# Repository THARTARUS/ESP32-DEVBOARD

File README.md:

# ESP32-DEVBOARD
this board is not tested (yet).
this devboard have:
1)  1 esp32-solo module
2)  1 I2C LUX SENSOR (VEML6030), with 0x10 ADDRESS
2)  2 12mm button with RC filter
3)  6 LED RED on 0603 format drived with only 3 I/O
4)  1 rotary ENCODER (to choose if you want the HOLLOWSHAFT named EC10E1260502 or a BOURNS encoder from the family PEC12R)
5)  1 BUZZER (SMD or 12mmTHT) or a SPEAKER (you can choose which one you need) drived with a NMOSFET sot23
6)  1 POWER OUTPUT (a sot23 PMOSFET drived by an NPN BJT)
7)  1 I2C temperature and humidity sensor (AHT20), with 0x37 ADDRESS
8)  1 2.42inch OLED display with I2C comunication, with 0x3C or 0x3D ADDRESS
9)  1 USB type-C connection (without PD) with a serial converter
10) 1 battery backup circuit with a charger (MCP7833 with charging up to 1A) and protection circuit DW01A)
11) 1 Power connection with USB/5V external supply priority and a DCDC with high efficency and VIn from 6V to 15V
12) 1 switching DCDC BUCKBOOST for the 3.3V power supply of the devboard and external circuit (with external load up to 600mA )
13) 1 expansion I/O with:
                          2 only analog INPUT
                          1 3x2 pin for external 3.3V supply need
                          1 JST-PH 1x04 for STEMMA and QWIIC sensor connected to the I2C line used for the other component on the board
                          1 SPI port (VPSI for DMA working) and the I2C connected with the JST-PH comunication line

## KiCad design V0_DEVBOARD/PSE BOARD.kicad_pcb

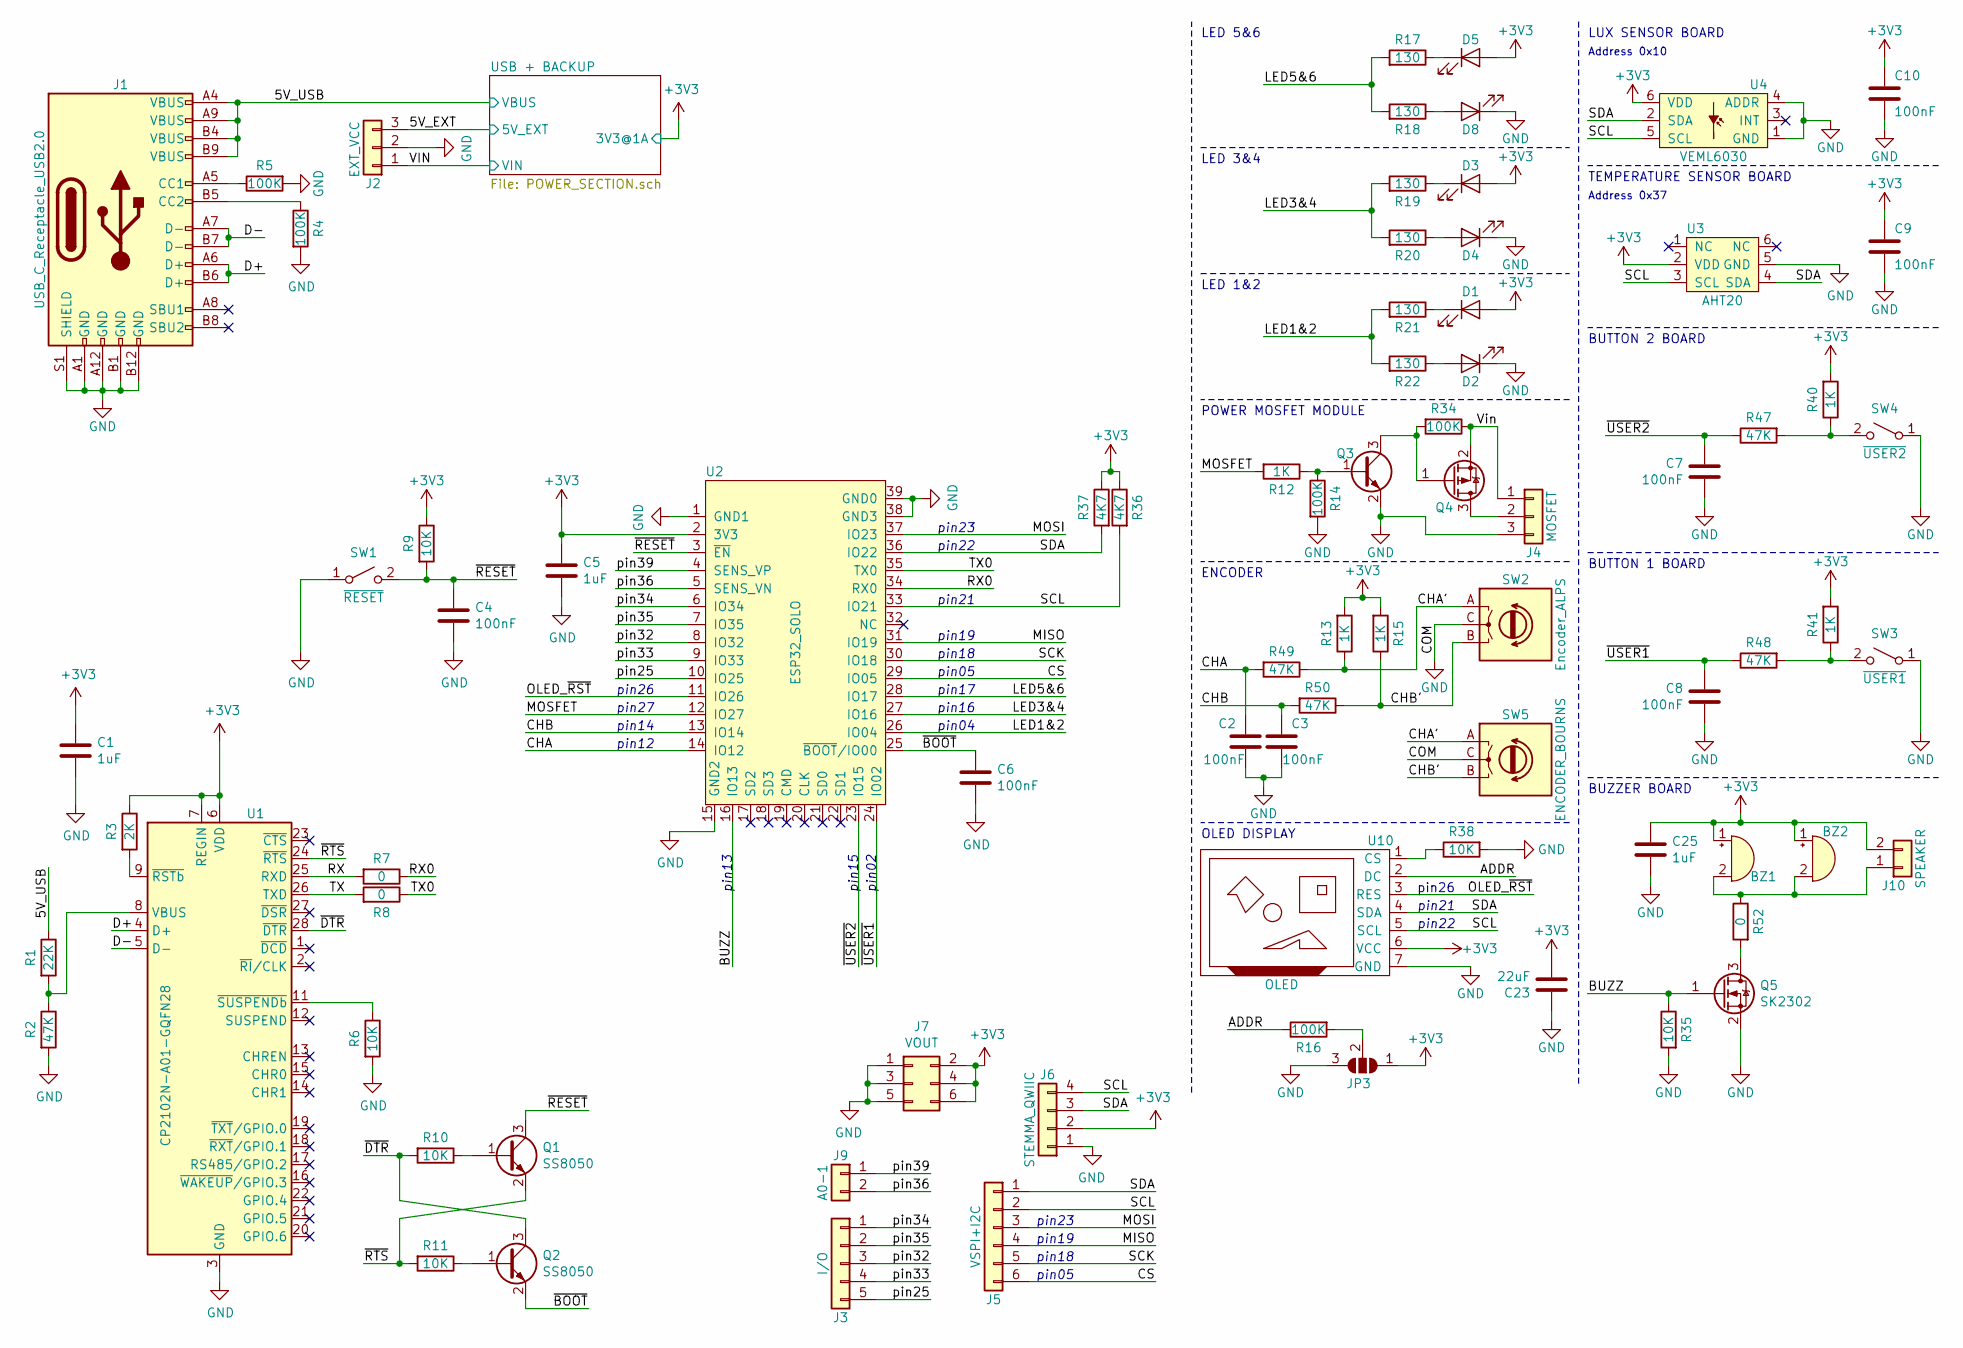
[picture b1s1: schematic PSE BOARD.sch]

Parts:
BZ1: Buzzer; Buzzer_CUI_CPT-9019S-SMT
BZ2: Buzzer; Buzzer_12x9.5RM7.6
C1, C5, C25: 1uF; C_0805_2012Metric
C2, C3, C4, C6, C7, C8, C9, C10: 100nF; C_0402_1005Metric
C23: 22uF; C_1210_3225Metric
D1, D2, D3, D4, D5, D8: LED; LED_0603_1608Metric_Castellated
J1: USB_C_Receptacle_USB2.0; USB_C_Receptacle_HRO_TYPE-C-31-M-12
J2: EXT_VCC; PinHeader_1x03_P2.54mm_Vertical
J3: I/O; PinHeader_1x05_P2.54mm_Vertical
J4: MOSFET; PinHeader_1x03_P2.54mm_Vertical
J5: VSPI+I2C; PinHeader_1x06_P2.54mm_Vertical
J6: STEMMA_QWIIC; JST_SH_SM04B-SRSS-TB_1x04-1MP_P1.00mm_Horizontal
J7: VOUT; PinHeader_2x03_P2.54mm_Vertical
J9: A0-1; PinHeader_1x02_P2.54mm_Vertical
J10: SPEAKER; JST_PH_B2B-PH-K_1x02_P2.00mm_Vertical
JP3: SolderJumper_3_Open; SolderJumper-3_P1.3mm_Open_RoundedPad1.0x1.5mm
Q1, Q2: SS8050; SOT-323_SC-70
Q3: LMBT3904WT1G; SOT-323_SC-70
Q4: SSM3J332R; SOT-23F
Q5: SK2302; SOT-23
R1: 22K; R_0402_1005Metric
R2, R47, R48, R49, R50: 47K; R_0402_1005Metric
R3: 2K; R_0402_1005Metric
R4, R5, R14, R16, R34: 100K; R_0402_1005Metric
R6, R9, R10, R11, R35, R38: 10K; R_0402_1005Metric
R7, R8: 0; R_0402_1005Metric
R12, R13, R15, R40, R41: 1K; R_0402_1005Metric
R17, R18, R19, R20, R21, R22: 130; R_0603_1608Metric
R36, R37: 4K7; R_0402_1005Metric
R52: 0; R_0805_2012Metric
SW1: ~RESET~; SW_SPST_4.5mmx4.5mm
SW2: Encoder_ALPS; RotaryEncoder_Alps_EC10E_HORIZONTAL
SW3: ~USER1~; 12x12mm_THT_OMRON_B3F
SW4: ~USER2~; 12x12mm_THT_OMRON_B3F
SW5: ENCODER_BOURNS; PEC12R
U1: CP2102N-A01-GQFN28; QFN-28-1EP_5x5mm_P0.5mm_EP3.35x3.35mm
U2: ESP32_SOLO; ESP32-WROOM-32
U3: AHT20; AHT20_package
U4: VEML6030; VEML6030_PACKAGE
U10: OLED

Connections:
+3V3: BZ1.1 (-), BZ2.1 (-), C1.1, C5.1, C9.1, C10.1, C23.2, C25.1, D1.2 (A), D3.2 (A), D5.2 (A), J6.2, J7.2, J7.4, J7.6, J10.2, JP3.1 (A), R3.1, R9.1, R13.2, R15.2, R36.1, R37.1, R40.2, R41.2, U1.6 (VDD), U1.7 (REGIN), U2.2 (3V3), U3.2 (VDD), U4.6 (VDD), U10.6 (VCC); also elsewhere on the board
/5V_EXT: J2.3; also elsewhere on the board
/5V_USB: J1.A4 (VBUS), J1.A9 (VBUS), J1.B4 (VBUS), J1.B9 (VBUS), R1.1; also elsewhere on the board
/ADDR: R16.1, U10.2 (DC)
/BUZZ: Q5.1 (G), R35.1, U2.16 (IO13)
/CHA: C2.1, R49.2, U2.14 (IO12)
/CHA': R13.1, R49.1, SW2.A, SW5.A
/CHB: C3.1, R50.2, U2.13 (IO14)
/CHB': R15.1, R50.1, SW2.B, SW5.B
/CS: J5.6, U2.29 (IO05)
/D+: J1.A6 (D+), J1.B6 (D+), U1.4 (D+)
/D-: J1.A7 (D-), J1.B7 (D-), U1.5 (D-)
/LED1&2: R21.2, R22.2, U2.26 (IO04)
/LED3&4: R19.2, R20.2, U2.27 (IO16)
/LED5&6: R17.2, R18.2, U2.28 (IO17)
/MISO: J5.4, U2.31 (IO19)
/MOSFET: R12.2, U2.12 (IO27)
/MOSI: J5.3, U2.37 (IO23)
/OLED_~RST~: U2.11 (IO26), U10.3 (RES)
/RX: R7.2, U1.25 (RXD)
/RX0: R7.1, U2.34 (RX0)
/SCK: J5.5, U2.30 (IO18)
/SCL: J5.2, J6.4, R36.2, U2.33 (IO21), U3.3 (SCL), U4.5 (SCL), U10.5 (SCL)
/SDA: J5.1, J6.3, R37.2, U2.36 (IO22), U3.4 (SDA), U4.2 (SDA), U10.4 (SDA)
/TX: R8.2, U1.26 (TXD)
/TX0: R8.1, U2.35 (TX0)
/VIN: J2.1; also elsewhere on the board
/Vin: J4.1, Q4.2 (S), R34.1
/pin25: J3.5, U2.10 (IO25)
/pin32: J3.3, U2.8 (IO32)
/pin33: J3.4, U2.9 (IO33)
/pin34: J3.1, U2.6 (IO34)
/pin35: J3.2, U2.7 (IO35)
/pin36: J9.2, U2.5 (SENS_VN)
/pin39: J9.1, U2.4 (SENS_VP)
/~BOOT~: C6.1, Q2.2 (E), U2.25 (~BOOT~/IO00)
/~DTR: Q2.3 (C), R10.2, U1.28 (~DTR)
/~RESET~: C4.1, Q1.3 (C), R9.2, SW1.2 (B), U2.3 (~EN~)
/~RTS: Q1.2 (E), R11.2, U1.24 (~RTS)
/~USER1~: C8.1, R48.1, U2.24 (IO02)
/~USER2~: C7.1, R47.1, U2.23 (IO15)
GND: C1.2, C2.2, C3.2, C4.2, C5.2, C6.2, C7.2, C8.2, C9.2, C10.2, C23.1, C25.2, D2.1 (K), D4.1 (K), D8.1 (K), J1.A1 (GND), J1.A12 (GND), J1.B1 (GND), J1.B12 (GND), J1.S1 (SHIELD), J2.2, J4.3, J6.1, J7.1, J7.3, J7.5, JP3.3 (B), Q3.2 (E), Q5.2 (S), R2.2, R4.2, R5.2, R6.2, R14.2, R35.2, R38.2, SW1.1 (A), SW2.C, SW3.1 (A), SW4.1 (A), SW5.C, U1.3 (GND), U1.29 (GND), U2.1 (GND1), U2.15 (GND2), U2.38 (GND3), U2.39 (GND0), U3.5 (GND), U4.1 (GND), U4.4 (ADDR), U10.7 (GND); also elsewhere on the board
unnamed: BZ1.2 (+), BZ2.2 (+), J10.1, R52.1
unnamed: D1.1 (K), R21.1
unnamed: D2.2 (A), R22.1
unnamed: D3.1 (K), R19.1
unnamed: D4.2 (A), R20.1
unnamed: D5.1 (K), R17.1
unnamed: D8.2 (A), R18.1
unnamed: J1.A5 (CC1), R5.1
unnamed: J1.B5 (CC2), R4.1
unnamed: J4.2, Q4.3 (D)
unnamed: JP3.2 (C), R16.2
unnamed: Q1.1 (B), R10.1
unnamed: Q2.1 (B), R11.1
unnamed: Q3.1 (B), R12.1, R14.1
unnamed: Q3.3 (C), Q4.1 (G), R34.2
unnamed: Q5.3 (D), R52.2
unnamed: R1.2, R2.1, U1.8 (VBUS)
unnamed: R3.2, U1.9 (~RSTb)
unnamed: R6.1, U1.11 (~SUSPENDb)
unnamed: R38.1, U10.1 (CS)
unnamed: R40.1, R47.2, SW4.2 (B)
unnamed: R41.1, R48.2, SW3.2 (B)

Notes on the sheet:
pin26
pin27
pin14
pin23
LUX SENSOR BOARD
BUZZER BOARD
BUTTON 1 BOARD
BUTTON 2 BOARD
TEMPERATURE SENSOR BOARD
Address 0x10
Address 0x37
pin13
pin12
pin15
pin02
pin18
pin05
pin17
pin16
pin22
pin21
pin04
pin19
POWER MOSFET MODULE
LED 3&4
LED 1&2
ENCODER
LED 5&6
OLED DISPLAY

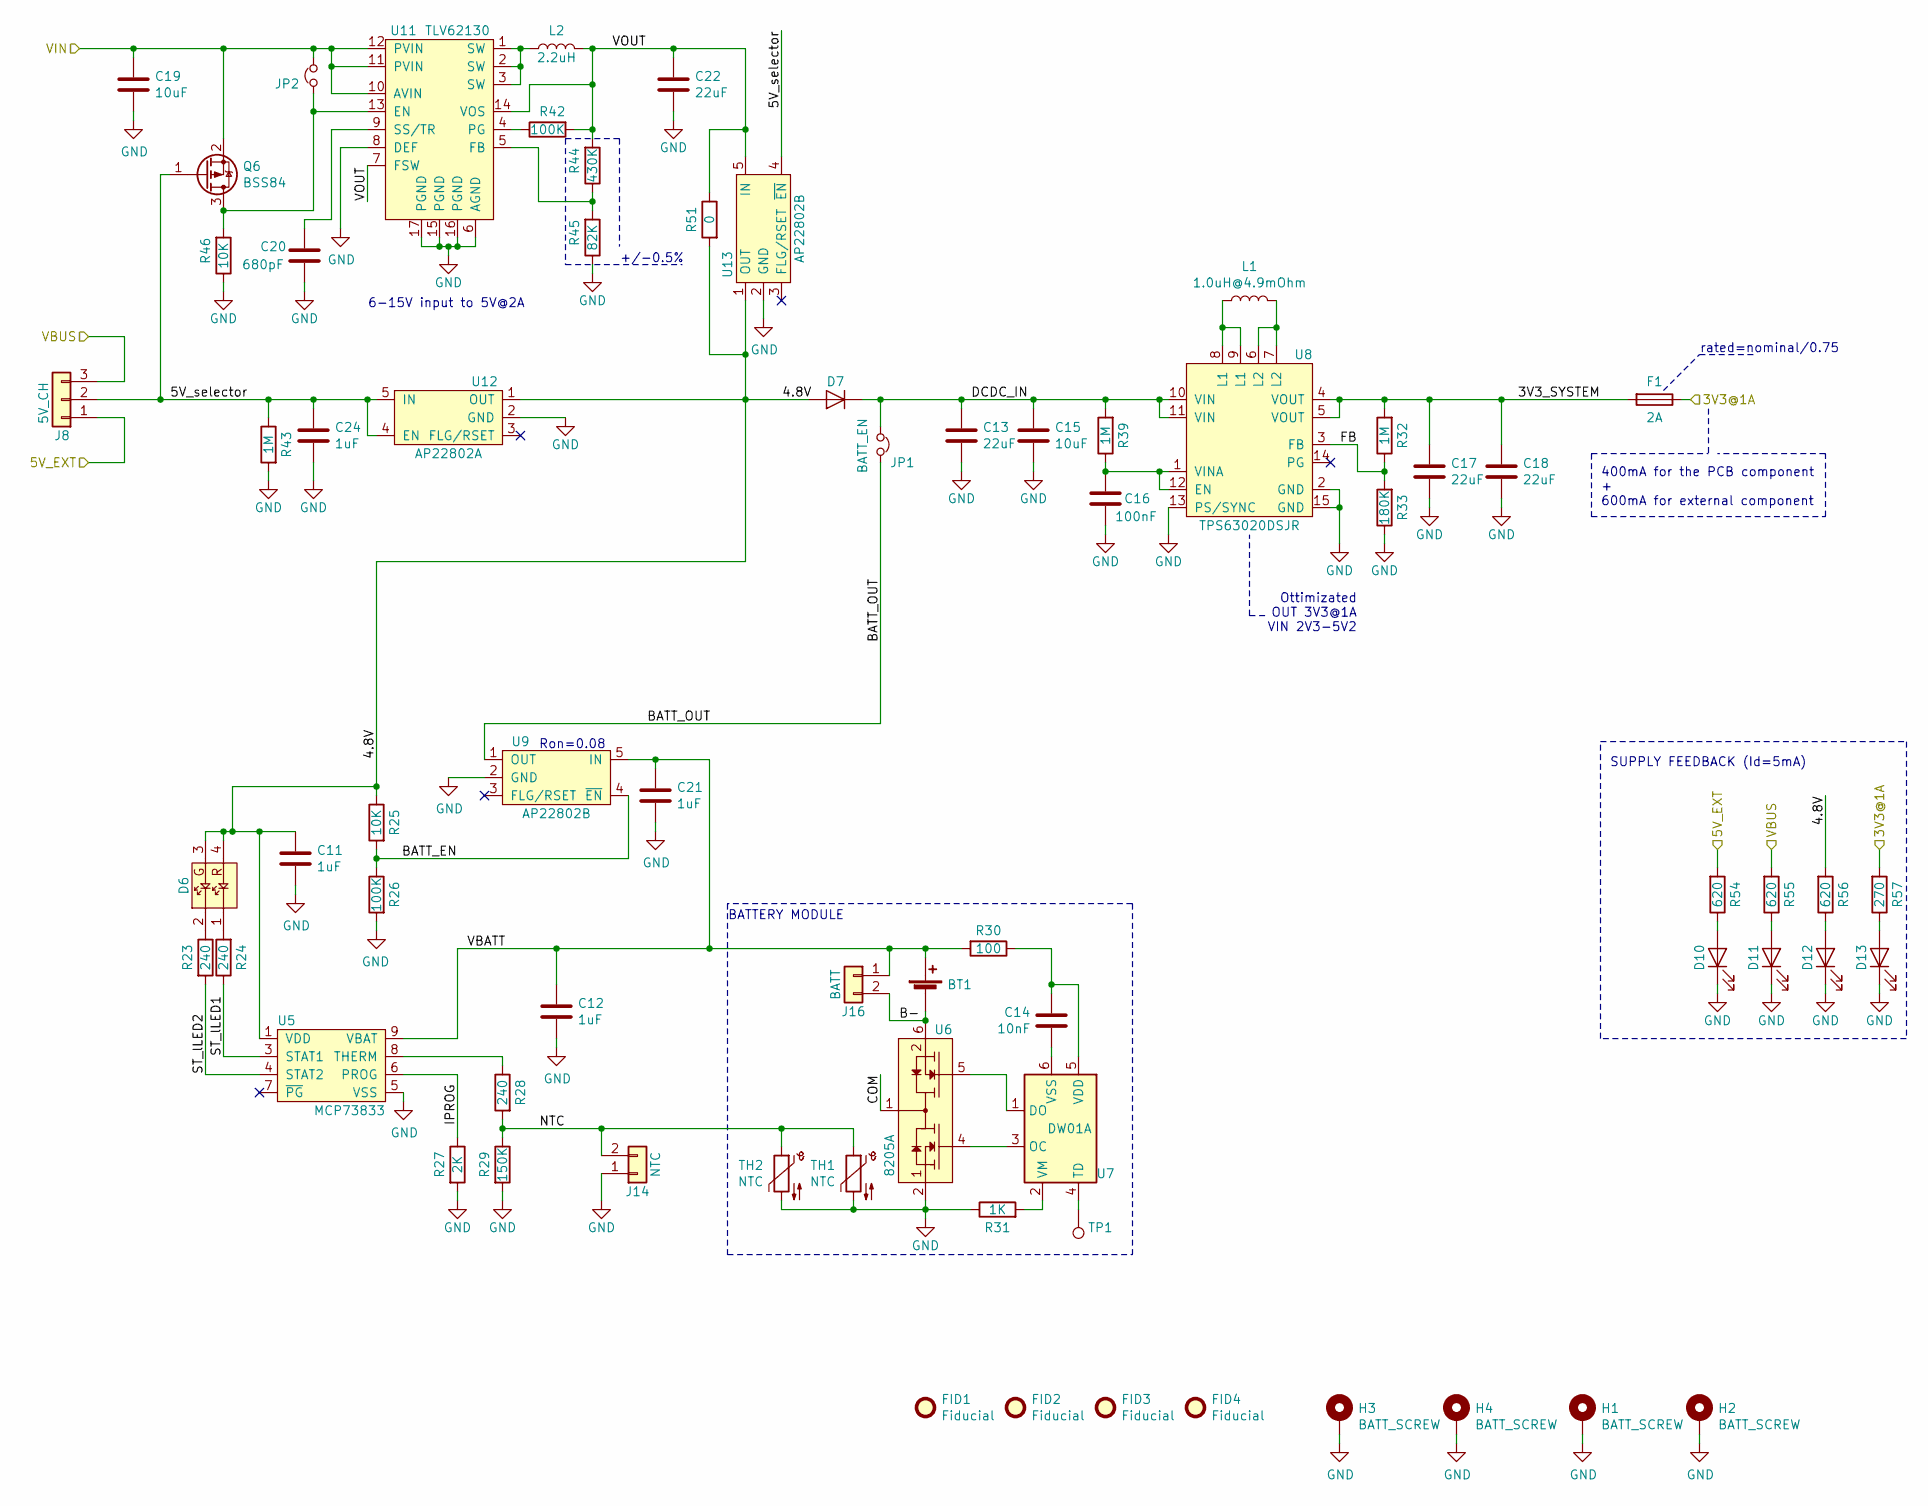
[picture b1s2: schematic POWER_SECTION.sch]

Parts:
BT1: Battery_Cell; BATT_18650_21700
C11, C12, C21, C24: 1uF; C_0805_2012Metric
C13: 22uF; C_1210_3225Metric
C14: 10nF; C_0402_1005Metric
C15: 10uF; C_1210_3225Metric
C16: 100nF; C_0402_1005Metric
C17, C18: 22uF; C_0805_2012Metric
C19: 10uF; C_0805_2012Metric
C20: 680pF; C_0603_1608Metric
C22: 22uF; C_1206_3216Metric
D6: LED_DUAL_COLOR; 11-22_S0MD_LED_EVERLIGHT
D7: D; D_SOD-123F
D10, D11, D12, D13: LED; LED_0402_1005Metric
F1: 2A; Fuse_1206_3216Metric
FID1, FID2, FID3, FID4: Fiducial; MountingHole_2.1mm
H1, H2, H3, H4: BATT_SCREW; MountingHole_2.7mm_M2.5_Pad_Via
J8: 5V_CH; PinHeader_1x03_P2.54mm_Vertical
J14: NTC; JST_PH_B2B-PH-K_1x02_P2.00mm_Vertical
J16: BATT; JST_PH_B2B-PH-K_1x02_P2.00mm_Vertical
JP1: BATT_EN; PinHeader_1x02_P2.54mm_Vertical
JP2: EN; JUMPER_0805_2012Metric
L1: 1.0uH@4.9mOhm; L_5.4x5.2x2.8mm
L2: 2.2uH; L_5.4x5.2x2.8mm
Q6: BSS84; SOT-23
R23, R24: 240; R_0603_1608Metric
R25, R46: 10K; R_0402_1005Metric
R26, R42: 100K; R_0402_1005Metric
R27: 2K; R_0402_1005Metric
R28: 240; R_0402_1005Metric
R29: 150K; R_0402_1005Metric
R30: 100; R_0402_1005Metric
R31: 1K; R_0402_1005Metric
R32, R39, R43: 1M; R_0402_1005Metric
R33: 180K; R_0402_1005Metric
R44: 430K; R_0402_1005Metric
R45: 82K; R_0402_1005Metric
R51: 0; R_0805_2012Metric
R54, R55, R56: 620; R_0402_1005Metric
R57: 270; R_0402_1005Metric
TH1, TH2: NTC; R_0603_1608Metric
TP1: TestPoint; TestPoint_Pad_D0.8mm
U5: MCP73833; DFN-10-1EP_3x3mm_P0.5mm_EP1.65x2.38mm_ThermalVias
U6: 8205A; TSSOP-8_4.4x3mm_P0.65mm
U7: DW01A; SOT-23-6
U8: TPS63020DSJR; Texas_S-PWSON-N14_ThermalVias
U9, U13: AP22802B; SOT-23-5
U11: TLV62130; VQFN-16-1EP_3x3mm_P0.5mm_EP1.68x1.68mm_ThermalVias
U12: AP22802A; SOT-23-5

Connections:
+3V3: F1.1, R57.2; also elsewhere on the board
/5V_EXT: J8.1, R54.2; also elsewhere on the board
/5V_USB: J8.3, R55.2; also elsewhere on the board
/USB + BACKUP/3V3_SYSTEM: C17.1, C18.1, F1.2, R32.2, U8.4 (VOUT), U8.5 (VOUT)
/USB + BACKUP/4.8V: C11.1, D6.3, D6.4, D7.2 (A), R25.1, R51.2, R56.2, U5.1 (VDD), U5.2 (VDD), U12.1 (OUT), U13.1 (OUT)
/USB + BACKUP/5V_selector: C24.1, J8.2, Q6.1 (G), R43.1, U12.4 (EN), U12.5 (IN), U13.4 (~EN~)
/USB + BACKUP/B-: BT1.2 (-), J16.2, U6.6, U6.7 (S2)
/USB + BACKUP/BATT_EN: R25.2, R26.1, U9.4 (~EN~)
/USB + BACKUP/BATT_OUT: JP1.2, U9.1 (OUT)
/USB + BACKUP/COM: U6.1, U6.8 (D12)
/USB + BACKUP/DCDC_IN: C13.1, C15.1, D7.1 (K), JP1.1, R39.2, U8.10 (VIN), U8.11 (VIN)
/USB + BACKUP/FB: R32.1, R33.2, U8.3 (FB)
/USB + BACKUP/IPROG: R27.1, U5.6 (PROG)
/USB + BACKUP/NTC: J14.2, R28.2, R29.1, TH1.1, TH2.1
/USB + BACKUP/ST_lLED1: R24.1, U5.3 (STAT1)
/USB + BACKUP/ST_lLED2: R23.2, U5.4 (STAT2)
/USB + BACKUP/VBATT: BT1.1 (+), C12.1, C21.1, J16.1, R30.2, U5.9 (VBAT), U5.10 (VBAT), U9.5 (IN)
/USB + BACKUP/VOUT: C22.2, L2.2, R42.2, R44.2, R51.1, U11.7 (FSW), U11.14 (VOS), U13.5 (IN)
/VIN: C19.1, JP2.2, Q6.2 (S), U11.10 (AVIN), U11.11 (PVIN), U11.12 (PVIN); also elsewhere on the board
GND: C11.2, C12.2, C13.2, C15.2, C16.2, C17.2, C18.2, C19.2, C20.1, C21.2, C22.1, C24.2, D10.1 (K), D11.1 (K), D12.1 (K), D13.1 (K), H1.1, H2.1, H3.1, H4.1, J14.1, R26.2, R27.2, R29.2, R31.1, R33.1, R43.2, R45.1, R46.1, TH1.2, TH2.2, U5.5 (VSS), U5.11 (VSS), U6.2, U6.3 (S1), U8.2 (GND), U8.13 (PS/SYNC), U8.15 (GND), U9.2 (GND), U11.6 (AGND), U11.8 (DEF), U11.15 (PGND), U11.16 (PGND), U11.17 (PGND), U12.2 (GND), U13.2 (GND); also elsewhere on the board
unnamed: C14.1, U7.6 (VSS)
unnamed: C14.2, R30.1, U7.5 (VDD)
unnamed: C16.1, R39.1, U8.1 (VINA), U8.12 (EN)
unnamed: C20.2, U11.9 (SS/TR)
unnamed: D6.1, R24.2
unnamed: D6.2, R23.1
unnamed: D10.2 (A), R54.1
unnamed: D11.2 (A), R55.1
unnamed: D12.2 (A), R56.1
unnamed: D13.2 (A), R57.1
unnamed: JP2.1, Q6.3 (D), R46.2, U11.13 (EN)
unnamed: L1.1, U8.8 (L1), U8.9 (L1)
unnamed: L1.2, U8.6 (L2), U8.7 (L2)
unnamed: L2.1, U11.1 (SW), U11.2 (SW), U11.3 (SW)
unnamed: R28.1, U5.8 (THERM)
unnamed: R31.2, U7.2 (VM)
unnamed: R42.1, U11.4 (PG)
unnamed: R44.1, R45.2, U11.5 (FB)
unnamed: TP1.1, U7.4 (TD)
unnamed: U6.4, U7.3 (OC)
unnamed: U6.5, U7.1 (DO)

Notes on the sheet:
Ottimizated OUT 3V3@1A VIN 2V3-5V2
rated=nominal/0.75
BATTERY MODULE
Ron=0.08
6-15V input to 5V@2A
+/-0.5%
400mA for the PCB component + 600mA for external component
SUPPLY FEEDBACK (Id=5mA)

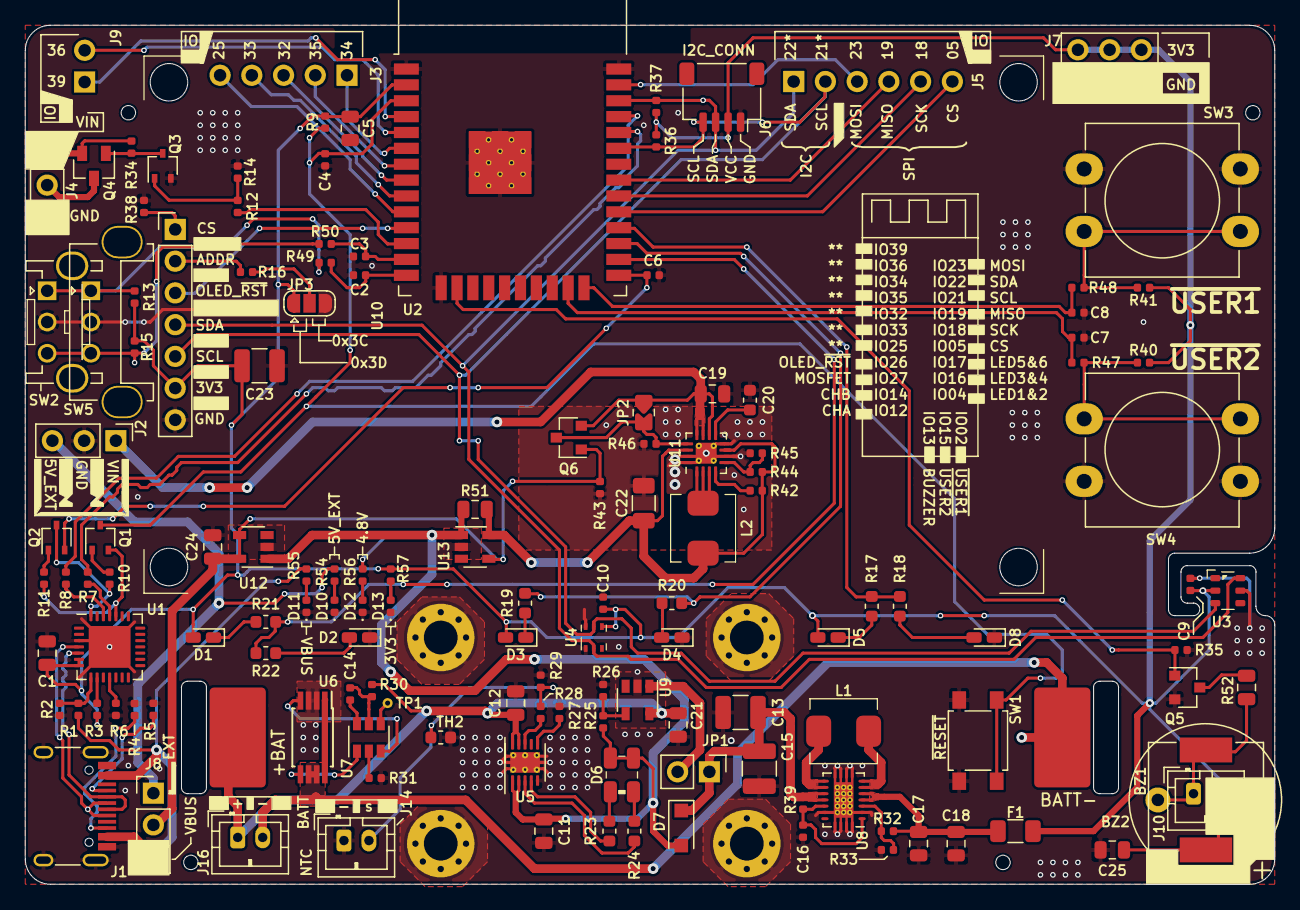
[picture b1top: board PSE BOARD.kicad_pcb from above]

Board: 2 copper layers, 100.0 x 68.8 mm, 149 parts (1 on the bottom side), 100 nets.

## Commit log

2020-09-09 prima relazione
2020-09-09 kicad file PT1
2020-09-09 3d file upload
2020-09-09 kicad library upload
